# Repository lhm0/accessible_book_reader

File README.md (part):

# Accessible Book Reader

Software- und Hardware-Repository fuer den `Accessible Book Reader` (`ABR`).

## Lizenz

Der Accessible Book Reader ist ein Open-Source-/Open-Hardware-Projekt mit
starkem Copyleft. Wegen der unterschiedlichen Arten von Projektmaterial gilt
ein klar abgegrenztes Mehrfachlizenzmodell:

- eigener Software- und Firmwarecode: `GPL-3.0-or-later`
- eigene Elektronik-, Mechanik- und sonstige Hardwaredesigns:
  `CERN-OHL-S-2.0`
- Dokumentation und eindeutig eigene Medien: `CC-BY-SA-4.0`
- Fremdbibliotheken: unveraendert unter ihrer jeweiligen Originallizenz

Die mit Google Cloud Text-to-Speech erzeugten Systemansagen enthalten einen
eigenen [Herkunfts- und Nutzungshinweis](system_audio/messages/README.md).

Die GPL und CERN-OHL-S erlauben auch kommerzielle Nutzung, verlangen bei der
Weitergabe abgeleiteter Software beziehungsweise Hardware aber die jeweils
vorgesehene Bereitstellung des vollstaendigen Quellmaterials unter den
Copyleft-Bedingungen. Eine allgemeine Ausnahme fuer geschlossene kommerzielle
Weiterentwicklungen besteht nicht.

Die verbindliche Abgrenzung, Ausnahmen fuer Fremdcode und Hinweise zu nicht
mitlizenzierten Drittmaterialien stehen in [LICENSE.md](LICENSE.md); die
vollstaendigen Lizenztexte liegen unter [`LICENSES/`](LICENSES/). Hinweise zu
eingebundenem Fremdcode stehen in
[THIRD_PARTY_NOTICES.md](THIRD_PARTY_NOTICES.md). Fuer
Beitraege gelten [CONTRIBUTING.md](CONTRIBUTING.md) und die
[Contributor License Agreement](CLA.md). Die Contributor-Vereinbarung erhaelt
das Eigentum der Beitragenden, erlaubt dem Projektinhaber aber zusaetzlich eine
parallele kommerzielle Lizenzierung fuer spaetere Firmenkooperationen.
Firmenkooperationen, die von diesen oeffentlichen Lizenzen abweichen sollen,
erfordern einen separaten Entwicklungs- und Lizenzvertrag mit den jeweiligen
Rechteinhabern.

Es wurde keine Patent- oder Freedom-to-Operate-Recherche durchgefuehrt. Die
Lizenzen koennen nur Rechte einraeumen, ueber die der jeweilige Lizenzgeber
verfuegen darf; sie geben keine Zusicherung, dass Herstellung, Nutzung oder
Vertrieb keine Rechte Dritter beruehren. Der vollstaendige Hinweis und die
besondere Abgrenzung zwischen privatem Nachbau und kommerzieller Nutzung
stehen in [PATENT_NOTICE.md](PATENT_NOTICE.md).

Der Projektstand ist inzwischen ueber den reinen OCR-/TTS-Prototyp hinaus:

- realer Capture-Pfad mit `2` Pi-Kameras ist verifiziert
- `RapidOCR` laeuft stabil auf dem Pi
- `Google Cloud TTS` ist integriert
- Bedienpanel, NFC-Buchkontext, Seitenspeicherung und automatische
  Seitenausgabe sind implementiert
- E-Mail-Fernwartung fuer Datei-Download und kontrollierten Datei-Upload ist
  implementiert
- mehrere gespeicherte WLAN-Profile koennen automatisch ausgewaehlt oder
  gezielt umgeschaltet werden
- zentrale Buchsprachenprofile fuer Deutsch und U.S.-Englisch steuern
  Runtime-TTS, Kapitelansagen und die RapidOCR-Modellauswahl; Deutsch bleibt
  der kompatible Default
- neue NFC-Buecher speichern ihre Sprache dauerhaft in `book.json`; OCR,
  Ingest, Kapitel, Zusammenfassungen und TTS verhindern gemischte Buchdaten

Der aktuelle Entwicklungsschwerpunkt liegt jetzt auf:

- Stabilisierung und Feinschliff der neuen Abschnitts- und Summary-Ebene
- Langzeittest des integrierten PN5180-Zwei-Reader-Pfads mit
  `ISO14443A` und `ISO15693`

## Aktueller Produktpfad

Der derzeit bevorzugte reale Lauf auf dem Raspberry Pi 5 ist:

- Runtime: `hardware/control_panel_service.py`
- TTS fuer Seiten: `Google Cloud TTS`, Stimme aus dem aktiven Sprachprofil
- Systemhinweise: vorproduzierte WAV-Dateien aus dem Unterordner des aktiven
  Sprachprofils (`system_audio/messages/de/` oder `system_audio/messages/en/`)
- Buchidentifikation: `PN5180`-Gateway ueber UART
- Audiohardware: `MAX98357A` ueber I2S; ALSA-`default` muss systemweit per
  symbolischem Kartennamen auf diese Karte zeigen

Im Runtime-Pfad gilt aktuell:

- beim Start wird die PN5180-Abfrage sofort per `STATUS_START` angestossen
- die beiden Fotos werden aufgenommen, bevor das Ergebnis per `STATUS_FETCH`
  fuer Buchzuordnung und Orientierung abgeholt wird
- `ISO14443A` ist der fuehrende Buchschluessel; ein gleichzeitig gelesener
  `ISO15693`-Tag wird im Buchordner als alternative Zuordnung gespeichert
- Reader 2 kennzeichnet Orientierung 1: die beim Capture erzeugte
  Links-/Rechts-Zuordnung bleibt bestehen
- Reader 1 kennzeichnet Orientierung 2: `case/left.jpg` und
  `case/right.jpg` werden direkt nach `STATUS_FETCH` vertauscht
- danach wird `case/right.jpg` einmalig um `180` Grad gedreht; in der
  OCR-Vorverarbeitung erfolgt keine weitere feste Seitendrehung
- beide Seiten werden zuerst komplett aufgenommen
- danach wird links vor rechts verarbeitet
- Bildvorbereitung, OCR, `PageIngestor` und TTS starten zunaechst nur fuer die
  linke Seite
- waehrend die linke Seite bereits abgespielt wird, folgen Bildvorbereitung,
  OCR, `PageIngestor` und TTS fuer die rechte Seite

## Was Jetzt Implementiert Ist

### Laufende Geraetelogik

- langlebiger Frontpanel-Monitor
- `Start / Stop / NFC` fuer echten Lauf `capture -> Bildvorbereitung -> OCR -> page-ingest`
- Heartbeat-Signal waehrend der Wartezeit bis zur ersten Seitenaudio
- abbrechbare Seitenausgabe
- Lautstaerkeregelung ueber EC11-Flankeninterrupts mit threadsicherem
  Sollwert; wirkt blockweise auch waehrend `bing.wav` und Seitenaudio
- Buch-Loeschdialog ueber Dreifachtaste und `EC11`-Taster
- persistente, buchweise Nutzerstatistik fuer gescannte Seiten,
  Vorlesedauer und beide Zusammenfassungsfunktionen; taeglicher E-Mail-Report
  fuer den Zeitraum `04:00` bis `04:00`, auch an Tagen ohne Nutzung

### Buch- und Seitendaten

- Speicherung pro Buch unter `library/<TAG_ID>/`
- alternative ISO15693-Zuordnungen unter
  `library/<ISO14443A_TAG_ID>/iso15693_tag_ids.txt`
- `BookStore`
- `PageIngestor`
- `ChapterAssembler` fuer 10-20 Seiten lange Abschnitte mit Mid-Page-Grenzen
- `SummaryManager` fuer Abschnitts- und Gesamtzusammenfassungen ueber Gemini
- `PageRecord`-Ablage pro Seite
- `ChapterRecord`-Ablage pro Abschnitt
- `ScanRecord`-Ablage pro Doppelseite
- automatische Seitenausgabe auf Basis von `speak_text`

### Bereits sauber behandelte Textfaelle

- fehlende Seitenzahl auf nur einer Seite eines vollstaendigen Doppelseiten-
  Reports
- mehrere Kapitelmarker auf einer Seite
- reine Ueberschriftenseiten wie `INTERMEZZO`
- unvollstaendige Satzreste ueber Seiten hinweg
- Worttrennungen ueber Zeilen und ueber die linke/rechte Seitenkante
- gesperrt gesetzte Woerter wie `U E B E R S C H R I F T` werden fuer die
  Ausgabe ohne Buchstabenabstaende geschrieben
- kurze, vollstaendig grossgeschriebene Ueberschriften werden im
  `speak_text` lesbar geschrieben und als eigener Absatz markiert
- deutsche Vorlesetexte ersetzen `Dr.` durch `Doktor` und `Notre-Dame` durch
  `Notre Damm`; der originalgetreue `clean_text` bleibt unveraendert
  (bereits gespeicherte Seiten erhalten diese Ersetzungen erst bei erneutem
  Page-Ingest)
- kurze eingeklammerte OCR-Artefakte mit Ziffern werden nicht als Satzrest
  auf die Folgeseite uebernommen
- Kapitelansagen als Kardinalzahlen wie `Kapitel zwei`
- deutliche SSML-Pausen vor und nach Kapitelansagen

Wichtig zum aktuellen Satzrest-Verhalten:

- der Satzrest einer rechten Seite wird zusaetzlich unter
  `library/<TAG_ID>/state/pending_right_tail_fragment.json` gehalten
- fehlt bei einer frueh ingestierten linken Einzelseite die Seitenzahl, wird
  genau dieser Pending-Speicher fuer den Uebergang zur naechsten Seite genutzt

## Was Jetzt Neu Hinzugekommen Ist

- Abschnitte werden nach jedem Ingest aus vorhandenen `PageRecord`s gebildet
- Abschnittsenden liegen an der ersten erkannten Kapitelgrenze im Fenster
  `10..20` Seiten
- ohne Kapitelmarke endet ein Abschnitt am letzten vollstaendigen Absatz der
  `20.` Seite; die Folgegrenze wird persistent gespeichert
- abgeschlossene Abschnitte werden unter `library/<TAG_ID>/chapters/`
  gespeichert
- neue Abschnittszusammenfassungen werden direkt beim Erzeugen eines neuen
  Abschnitts ueber Gemini geschrieben
- `Kapitel-/Letzte-Seiten-Zusammenfassung` spricht die letzte
  Abschnittszusammenfassung, erzeugt oder aktualisiert sie bei Bedarf und
  signalisiert waehrenddessen per Intro plus `bing`-Heartbeat
- liegt nach dem letzten abgeschlossenen Abschnitt bereits weiterer Text vor,
  kombiniert dieselbe Taste dessen gespeicherte Zusammenfassung mit dem
  offenen Text zu einer temporaeren aktuellen Rueckschau; diese wird nur
  vorgelesen und nicht gespeichert
- vor dem ersten abgeschlossenen Abschnitt wird der vorhandene offene Text
  allein temporaer zusammengefasst
- `Buch-Zusammenfassung` erzeugt und spricht ein aktuelles
  "Was bisher geschah" in Kapitelreihenfolge, ebenfalls mit Intro plus
  `bing`-Heartbeat
- wenn noch keine Zusammenfassung vorliegt, spielt die Runtime
  `keine_zusammenfassung`

## Installation

Die README ist der Einstieg fuer eine Neuinstallation. Die ausfuehrliche,
hardwarebezogene Schritt-fuer-Schritt-Anleitung steht in
[docs/RASPBERRY_PI_SETUP.md](docs/RASPBERRY_PI_SETUP.md); der abschliessende
Funktionstest steht in
[docs/RASPBERRY_PI_SMOKETEST.md](docs/RASPBERRY_PI_SMOKETEST.md).

### 1. Raspberry Pi vorbereiten und Repository auschecken

Empfohlen ist Raspberry Pi OS Lite (64-bit). Nach dem ersten Boot und dem
Systemupdate werden die benoetigten Systempakete installiert:

```bash
sudo apt update
sudo apt full-upgrade -y
sudo apt install -y \
  git curl ca-certificates \
  build-essential pkg-config \
  python3 python3-venv python3-pip python3-dev \
  tesseract-ocr tesseract-ocr-deu \
  libgl1 libopenblas-dev \
  espeak-ng alsa-utils pulseaudio-utils \
  htop tmux

mkdir -p ~/src
git clone https://github.com/lhm0/accessible_book_reader.git ~/src/abr
cd ~/src/abr
```

Die Kameras, der Header-UART und der MAX98357A benoetigen zusaetzlich die in
[docs/RASPBERRY_PI_SETUP.md](docs/RASPBERRY_PI_SETUP.md) beschriebenen
Eintraege in `/boot/firmware/config.txt` sowie die dort dokumentierte
`/etc/asound.conf`. Die Repository-Datei `config.txt` ist eine Referenz fuer
die verifizierte Hardware, darf aber nicht ungeprueft eine vorhandene
Boot-Konfiguration ersetzen. Anschliessend neu starten und Kameras, UART und
Audio wie in der Setup-Anleitung pruefen.

Die Firmware und Verdrahtung des bevorzugten PN5180-Gateways sind unter
[hardware/pn5180_gateway/README.md](hardware/pn5180_gateway/README.md)
dokumentiert. Alternativ steht der PN532-Pfad unter
[hardware/pn532_gateway/README.md](hardware/pn532_gateway/README.md).

### 2. Python-Umgebung installieren

Empfohlen ist eine frische virtuelle Umgebung mit dem normalen `python3`,
nicht mit dem PlatformIO-Python und nicht aus einem anderen Rechner kopiert.

```bash
cd ~/src/abr
python3 -m venv .venv
source .venv/bin/activate
python -m pip install --upgrade pip
python -m pip install -e ".[ocr-rapidocr,dev,tts-google]"
```

Optional:

```bash
pip install ".[ocr-tesseract]"
pip install ".[ocr-paddle]"
```

### 3. Google Cloud fuer TTS und Zusammenfassungen einrichten

Der produktive Dienst benoetigt Application Default Credentials (`ADC`) eines
Google-Cloud-Projekts, in dem die verwendeten APIs und Abrechnung aktiviert
sind. Nach Installation des Google-Cloud-CLI fuer Raspberry Pi OS:

```bash
gcloud services enable \
  texttospeech.googleapis.com \
  aiplatform.googleapis.com \
  --project DEIN_PROJECT_ID
gcloud auth application-default login
gcloud auth application-default set-quota-project DEIN_PROJECT_ID
gcloud config set project DEIN_PROJECT_ID
```

Die Befehle legen die Anmeldedaten ausserhalb des Repositorys unter
`~/.config/gcloud/` ab. Keine Credential-Datei in das Projekt kopieren. Der
systemd-Installer setzt `HOME` auf das Home-Verzeichnis des installierenden
Benutzers, sodass der Dienst dieselben ADC-Daten findet. Alternativ kann ein
Service-Account ueber den von Google dokumentierten ADC-Mechanismus
bereitgestellt werden. Details und Testbefehle stehen in
[docs/RASPBERRY_PI_SETUP.md](docs/RASPBERRY_PI_SETUP.md).

### 4. Lokale Geraetekonfiguration und Dienste

Die Installer werden aus dem Repository mit `sudo` aufgerufen. Sie ermitteln
Benutzer, Home-Verzeichnis, Repository und `.venv` aus der aktuellen
Installation; ein bestimmter Benutzername oder absoluter Projektpfad ist
nicht erforderlich.

```bash
cd ~/src/abr
sudo deploy/install_language_switch.sh
sudo deploy/install_control_panel_service.sh
```

Damit wird `~/.config/abr/device.json` bei Bedarf mit Deutsch als Default
angelegt und der produktive Dienst installiert. Die Sprache kann danach mit
`sudo abr-language de` beziehungsweise `sudo abr-language en` gesetzt werden.
Details stehen in [docs/LANGUAGE_PROFILES.md](docs/LANGUAGE_PROFILES.md).

Weitere Funktionen sind optional:

```bash
# Gespeicherte NetworkManager-WLAN-Profile beim Boot vorbereiten
sudo deploy/install_wifi_autoconnect.sh

# Beim ersten Lauf mail.ini anlegen, dann ausfuellen und erneut aufrufen
sudo deploy/install_remote_mail.sh
sudo deploy/install_remote_mail.sh

# Erst nach eingerichteter mail.ini installieren
sudo deploy/install_usage_statistics.sh
```

WLAN-Zugangsdaten bleiben in NetworkManager; neue Profile werden mit den
Befehlen aus [docs/WIFI_PROFILES.md](docs/WIFI_PROFILES.md) interaktiv
angelegt. Die E-Mail-Konfiguration wird im folgenden Abschnitt sowie in
[docs/REMOTE_MAINTENANCE_EMAIL.md](docs/REMOTE_MAINTENANCE_EMAIL.md)
beschrieben.

### Lokale und generierte Konfigurationsdateien

| Pfad | Inhalt und Erzeugung | Im Repository? |
|---|---|---|
| `/boot/firmware/config.txt` | Kamera-, UART- und I2S-Konfiguration; manuell nach Pi-Setup-Anleitung | Nein |
| `/etc/asound.conf` | ALSA-Default fuer MAX98357A; manuell nach Pi-Setup-Anleitung | Nein |
| `~/.config/gcloud/` | Google ADC und Quota-Projekt; durch `gcloud` oder Service-Account | Nein |
| `~/.config/abr/device.json` | Buchsprache; durch `install_language_switch.sh` | Nein |
| `~/.config/abr/mail.ini` | Mailkonto und Empfaenger; neutrale Vorlage durch `install_remote_mail.sh` | Nein |
| NetworkManager-Profile | SSIDs und WLAN-Passwoerter; interaktiv mit `abr.wifi_profiles` | Nein |
| `/etc/systemd/system/abr-*.service` und `abr-*.timer` | Lokale Benutzer- und Projektpfade; durch die jeweiligen Dienst-Installer erzeugt | Nein |
| `calibration/out/cam0_planar.npz`, `cam1_planar.npz` | Mitgelieferte Referenzkalibrierung; fuer abweichende Kameramechanik neu erzeugen | Ja |

Es gibt keine erforderliche `.env`-Datei. API-Schluessel fuer optionale
experimentelle Backends werden nur ueber `OPENAI_API_KEY` beziehungsweise
`ELEVENLABS_API_KEY` aus der lokalen Prozessumgebung gelesen; der produktive
Google-Pfad verwendet ADC.

### 5. Installation pruefen

```bash
cd ~/src/abr
source .venv/bin/activate
python -m pytest -q
systemctl status abr-control-panel.service --no-pager -l
journalctl -u abr-control-panel.service -n 100 --no-pager
```

Danach den Hardware- und Runtime-Smoke-Test aus
[docs/RASPBERRY_PI_SMOKETEST.md](docs/RASPBERRY_PI_SMOKETEST.md)
durchfuehren.

### Lokale E-Mail-Konfiguration

Persoenliche Mailadressen, Benutzernamen und Passwoerter werden nicht im
Repository gespeichert. Der Mailbetrieb liest sie auf dem Raspberry Pi aus
`~/.config/abr/mail.ini`.

Eine Vorlage wird beim ersten Aufruf von
`sudo deploy/install_remote_mail.sh` mit Dateimodus `0600` angelegt. Danach
die lokale Datei bearbeiten:

```ini
[mail]
address = abr-device@example.com
recipient = owner@example.com
username = abr-device@example.com
password = PASSWORT_FUER_E_MAIL_PROGRAMME
smtp_host = smtp.example.com
smtp_port = 465
imap_host = imap.example.com
imap_port = 993
inbox = INBOX
```

`address` und `username` bezeichnen das Konto des Geraets. An `recipient`
gehen Fernwartungsdateien und Nutzungsberichte; nur exakt diese Adresse wird
zugleich als Absender fuer Upload-Mails akzeptiert. Die echten Werte bleiben
ausschliesslich in dieser lokalen, nicht versionierten Datei. Bei einer
bestehenden Installation ohne `recipient` wird aus Kompatibilitaetsgruenden
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
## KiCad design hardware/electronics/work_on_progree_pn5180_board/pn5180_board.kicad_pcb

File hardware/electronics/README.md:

# Electronics Uebersicht

Dieses Verzeichnis enthaelt die aktuellen KiCad-Hardwareprojekte des ABR-Aufbaus.

## Aktive Teilprojekte

- [abr_pi5_header](../../hardware/electronics/abr_pi5_header/abr_pi5_header.kicad_sch)
  - Hauptverdrahtung rund um den `Raspberry Pi 5`
  - Audio (`MAX98357A`), NFC-Anbindung, Bedien- und Lichtsignale

- [control_panel](../../hardware/electronics/control_panel/control_panel.kicad_sch)
  - separates Bedienpanel
  - `EC11` Drehencoder sowie Haupttaster wie `Button_Start`
  - eigene Produktionsdaten unter
    [production](../../hardware/electronics/control_panel/production)

- [LED_bar_long](../../hardware/electronics/LED_bar_long/LED_bar_long.kicad_sch)
  - aktuell gepflegte LED-Leiste fuer die Beleuchtung
  - Fertigungsdaten unter
    [production](../../hardware/electronics/LED_bar_long/production)

Aktueller Verdrahtungshinweis fuer den realen Scanneraufbau:

- die Beleuchtung wird jetzt getrennt links/rechts geschaltet
- `LED-left` haengt an einer MOSFET-Stufe auf `BCM12`
- `LED-right` haengt an einer MOSFET-Stufe auf `BCM13`

## Historischer Hinweis

Das fruehere Projekt `LED_bar_short` ist nicht mehr der aktive Pfad. Die aktuellen Arbeitsstaende liegen bei `LED_bar_long`, `control_panel` und `abr_pi5_header`.

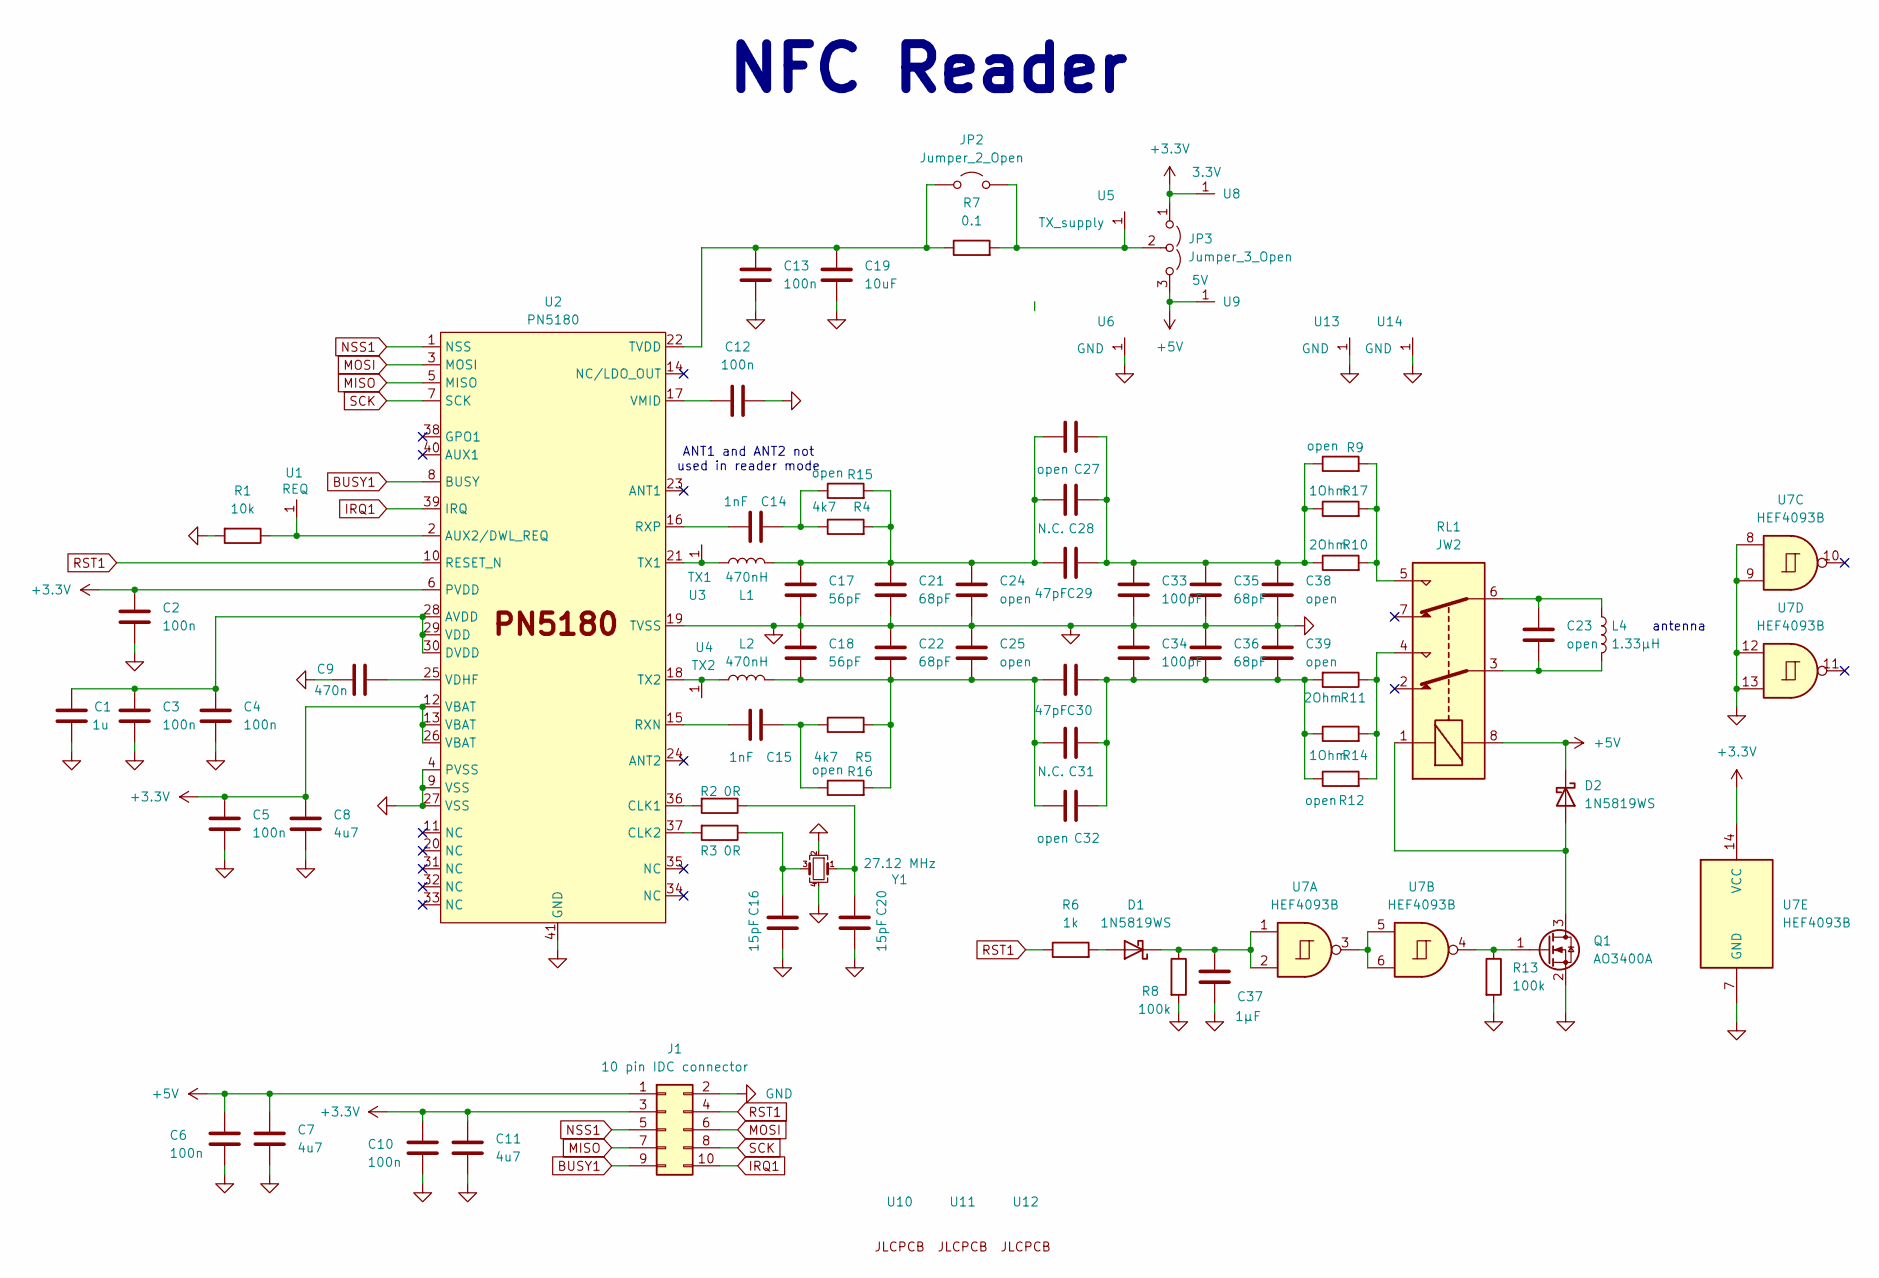
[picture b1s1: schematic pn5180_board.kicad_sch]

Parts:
C1: 1u; C_0603_1608Metric; LCSC C15849
C2, C3, C4, C5, C6, C10, C12, C13: 100n; C_0402_1005Metric; LCSC C1525
C7, C8, C11: 4u7; C_0603_1608Metric; LCSC C19666
C9: 470n; C_0603_1608Metric; LCSC C1623
C14, C15: 1nF; C_0402_1005Metric; LCSC C1523
C16, C20: 15pF; C_0402_1005Metric; LCSC C1548
C17, C18: 56pF; C_0603_1608Metric; LCSC C39148
C19: 10uF; C_0603_1608Metric; LCSC C96446
C21, C22, C35, C36: 68pF; C_0603_1608Metric; LCSC C28262
C23, C24, C25, C27, C32, C38, C39: open; C_aux
C28, C31: N.C.; C_0603_1608Metric
C29, C30: 47pF; C_0603_1608Metric; LCSC C1671
C33, C34: 100pF; C_0603_1608Metric; LCSC C14858
C37: 1µF; C_0603_1608Metric; LCSC C15849
D1, D2: 1N5819WS; D_SOD-323; LCSC C191023
J1: 10 pin IDC connector; IDC-Header_2x05_P2.54mm_Vertical_centered
JP2: Jumper_2_Open; SolderJumper-2_P1.3mm_Open_RoundedPad1.0x1.5mm
JP3: Jumper_3_Open; SolderJumper-3_P1.3mm_Open_RoundedPad1.0x1.5mm
L1, L2: 470nH; L_0603_1608Metric; LCSC C341701
L4: 1.33µH; NFC_antenna
Q1: AO3400A; SOT-23; LCSC C20917
R1: 10k; R_0402_1005Metric; LCSC C25744
R2, R3: 0R; R_0402_1005Metric; LCSC C17168
R4, R5: 4k7; R_0402_1005Metric; LCSC C25900
R6: 1k; R_0402_1005Metric; LCSC C11702
R7: 0.1; R_1206_3216Metric; LCSC C25334
R8, R13: 100k; R_0402_1005Metric; LCSC C25741
R9, R12, R15, R16: open; R_Axial_DIN0207_L6.3mm_D2.5mm_P10.16mm_Horizontal
R10, R11: 2Ohm; R_0603_1608Metric; LCSC C22977
R14, R17: 1Ohm; R_0603_1608Metric; LCSC C22936
RL1: JW2; Relay
U1: REQ; 1pin
U2: PN5180; HVQFN-40-1EP_6x6mm_P0.5mm_EP4.1x4.1mm_ThermalVias; LCSC C1526287
U3: TX1; 1pin
U4: TX2; 1pin
U5: TX_supply; 1pin
U6, U13, U14: GND; 1pin
U7: HEF4093B; SOIC-14_3.9x8.7mm_P1.27mm; LCSC C5456626
U8: 3.3V; 1pin
U9: 5V; 1pin
U10, U11, U12: JLC_tooling_hole
Y1: 27.12 MHz; Crystal_SMD_4Pin_A_3.2x2.5mm; LCSC C29975

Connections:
+3.3V: C2.1, C5.1, C8.1, C10.1, C11.1, J1.3, JP3.1 (A), U2.6 (PVDD), U2.12 (VBAT), U2.13 (VBAT), U2.26 (VBAT), U7.14 (VCC), U8.1 (pin)
+5V: C6.1, C7.1, D2.1 (K), J1.1, JP3.3 (B), RL1.8, U9.1 (pin)
BUSY1: J1.9, U2.8 (BUSY)
GND: C1.2, C2.2, C3.2, C4.2, C5.2, C6.2, C7.2, C8.2, C9.1, C10.2, C11.2, C12.2, C13.2, C16.2, C17.2, C18.1, C19.2, C20.2, C21.2, C22.1, C24.1, C25.2, C33.1, C34.2, C35.1, C36.2, C37.2, C38.1, C39.2, J1.2, Q1.2 (S), R1.2, R8.2, R13.2, U2.4 (PVSS), U2.9 (VSS), U2.19 (TVSS), U2.27 (VSS), U2.41 (GND), U6.1 (pin), U7.7 (GND), U7.8, U7.9, U7.12, U7.13, U13.1 (pin), U14.1 (pin), Y1.2, Y1.4
IRQ1: J1.10, U2.39 (IRQ)
MISO: J1.7, U2.5 (MISO)
MOSI: J1.6, U2.3 (MOSI)
NSS1: J1.5, U2.1 (NSS)
unnamed: C14.2, R4.1, R15.1
unnamed: C15.2, R5.1, R16.1
unnamed: C16.1, R3.1, Y1.3
unnamed: C17.1, C21.1, C24.2, C27.1, C28.1, C29.1, L1.2, R4.2, R15.2
unnamed: C18.2, C22.2, C25.1, C30.1, C31.1, C32.1, L2.2, R5.2, R16.2
unnamed: C20.1, R2.1, Y1.1
unnamed: C23.1, L4.2, RL1.3
unnamed: C23.2, L4.1, RL1.6
unnamed: C27.2, C28.2, C29.2, C33.2, C35.2, C38.2, R9.1, R10.1, R17.1
unnamed: C30.2, C31.2, C32.2, C34.1, C36.1, C39.1, R11.2, R12.1, R14.1
unnamed: D1.2 (A), R6.2
unnamed: C37.1, D1.1 (K), R8.1, U7.1, U7.2
unnamed: D2.2 (A), Q1.3 (D), RL1.1
unnamed: C13.1, C19.1, JP2.1 (A), R7.1, U2.22 (TVDD)
unnamed: JP2.2 (B), JP3.2 (C), R7.2, U5.1 (pin)
unnamed: Q1.1 (G), R13.1, U7.4
unnamed: R9.2, R10.2, R17.2, RL1.5
unnamed: R11.1, R12.2, R14.2, RL1.4
unnamed: R1.1, U1.1 (pin), U2.2 (AUX2/DWL_REQ)
unnamed: C1.1, C3.1, C4.1, U2.28 (AVDD), U2.29 (VDD), U2.30 (DVDD)
unnamed: R2.2, U2.36 (CLK1)
unnamed: R3.2, U2.37 (CLK2)
unnamed: C15.1, U2.15 (RXN)
unnamed: C14.1, U2.16 (RXP)
unnamed: L1.1, U2.21 (TX1), U3.1 (pin)
unnamed: L2.1, U2.18 (TX2), U4.1 (pin)
unnamed: C9.2, U2.25 (VDHF)
unnamed: C12.1, U2.17 (VMID)
unnamed: U7.3, U7.5, U7.6
RST1: J1.4, R6.1, U2.10 (RESET_N)
SCK: J1.8, U2.7 (SCK)

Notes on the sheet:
antenna
ANT1 and ANT2 not used in reader mode
NFC Reader

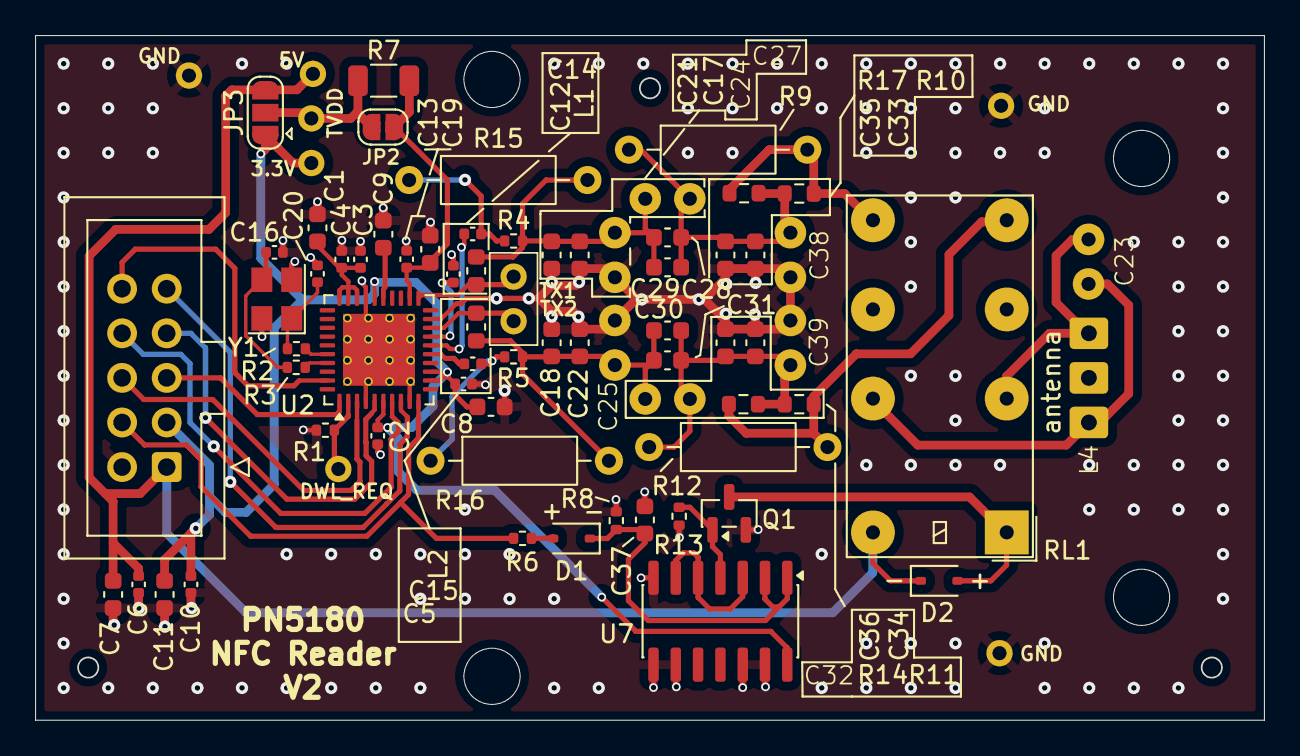
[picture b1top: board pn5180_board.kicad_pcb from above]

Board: 2 copper layers, 70.0 x 39.0 mm, 80 parts (0 on the bottom side), 39 nets.

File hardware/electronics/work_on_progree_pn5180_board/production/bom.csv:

Designator,Footprint,Quantity,Value,LCSC Part #
C1,0603,1,1u,C15849
"C10, C12, C13, C2, C3, C4, C5, C6",0402,8,100n,C1525
"C11, C7, C8",0603,3,4u7,C19666
"C14, C15",0402,2,1nF,C1523
"C16, C20",0402,2,15pF,C1548
"C17, C18",0603,2,56pF,C39148
C19,0603,1,10uF,C96446
"C21, C22, C35, C36",0603,4,68pF,C28262
"C23, C38, C39",C_aux,3,open,
"C24, C25, C27, C32",C_aux,4,open,
"C28, C31",0603,2,N.C.,
"C29, C30",0603,2,47pF,C1671
"C33, C34",0603,2,100pF,C14858
C37,0603,1,1µF,C15849
C9,0603,1,470n,C1623
"D1, D2",D_SOD-323,2,1N5819WS,C191023
J1,IDC-Header_2x05_P2.54mm_Vertical_centered,1,10 pin IDC connector,
JP2,SolderJumper-2_P1.3mm_Open_RoundedPad1.0x1.5mm,1,Jumper_2_Open,
"L1, L2",0603,2,470nH,C341701 
L4,NFC_antenna,1,1.33µH,
Q1,SOT-23,1,AO3400A,C20917
R1,0402,1,10k,C25744
"R10, R11",0603,2,2Ohm,C22977
"R12, R15, R16, R9",R_Axial_DIN0207_L6.3mm_D2.5mm_P10.16mm_Horizontal,4,open,
"R13, R8",0402,2,100k,C25741
"R14, R17",0603,2,1Ohm,C22936
"R2, R3",0402,2,0R,C17168
"R4, R5",0402,2,4k7,C25900
R6,0402,1,1k,C11702
R7,1206,1,0.1,C25334
RL1,Relay,1,JW2,
U1,1pin,1,REQ,
"U10, U11, U12",JLC_tooling_hole,3,~,
"U13, U14, U6",1pin,3,GND,
U2,HVQFN-40-1EP_6x6mm_P0.5mm_EP4.1x4.1mm_ThermalVias,1,PN5180,C1526287
U3,1pin,1,TX1,
U4,1pin,1,TX2,
U5,1pin,1,TX_supply,
U7,SOIC-14_3.9x8.7mm_P1.27mm,1,HEF4093B,C5456626
U8,1pin,1,3.3V,
U9,1pin,1,5V,
Y1,Crystal_SMD_4Pin_A_3.2x2.5mm,1,27.12 MHz,C29975

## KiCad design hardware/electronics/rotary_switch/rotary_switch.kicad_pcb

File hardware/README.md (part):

# Hardware Uebersicht

Dieses Verzeichnis enthaelt die hardwarebezogenen Teilprojekte fuer den
aktuellen ABR-Scannerstand.

## Struktur

- [pn532_gateway](../hardware/pn532_gateway/README.md)
  - RP2040-/Pico-Gateway fuer `2 x PN532`
  - UART-Protokoll zum `Raspberry Pi 5`
  - weiterhin als alternativer NFC-Pfad im Repo

- [pn5180_gateway](../hardware/pn5180_gateway/README.md)
  - RP2040-/Pico-Gateway fuer bis zu `2 x PN5180`
  - aktueller produktiver Buchkennungs-Pfad
  - aktueller technischer Arbeitsstand: `2 x PN5180`, sequentielle
    Reader-Freigabe ueber `RESET`, on-demand statt Polling

- [electronics](../hardware/electronics/README.md)
  - KiCad-Projekte fuer Pi-Header, Bedienpanel und LED-Bar

- [mechanics](../hardware/mechanics/README.md)
  - Fusion- und Exportdateien fuer den Scanneraufbau

## Wichtige Pi-Skripte

- [capture_double_page.py](../hardware/capture_double_page.py)
  - produktionsnaher Zwei-Kamera-Capture
  - schaltet `LED-left` und `LED-right` passend zur Aufnahme
  - erzeugt `raw`, `rectified`, `case`, `ocr` und `debug/page_1..2`
  - `--no-denoise` ist aktuell der bevorzugte schnelle Pfad

- [run_rapidocr.py](../hardware/run_rapidocr.py)
  - schlanker RapidOCR-Wrapper fuer vorbereitete `ocr/left.png` und
    `ocr/right.png`
  - schreibt `left.txt`, `right.txt` und `report.json`
  - bevorzugter Standard: `--orientation-mode off`

- [camera_test_server.py](../hardware/camera_test_server.py)
  - Browser-Livebildtest fuer die Pi-Kameras
  - optionales Fadenkreuz
  - Review-Modus fuer `raw`, `rectified`, `enhanced` und `ocr-overlay`

- [led_light_test.py](../hardware/led_light_test.py)
  - einfacher Test fuer `LED-left` auf `BCM12` und `LED-right` auf `BCM13`

- [control_panel_test.py](../hardware/control_panel_test.py)
  - einfacher GPIO-Test fuer Taster und `EC11`

- [control_panel_service.py](../hardware/control_panel_service.py)
  - aktueller produktionsnaher Runtime-Dienst
  - startet den echten Lauf `capture -> Bildvorbereitung -> OCR -> page-ingest`
  - liest Buch-Tags ueber NFC-Gateway
  - startet die PN5180-Abfrage beim Tastendruck mit `STATUS_START` und holt
    sie nach beiden Aufnahmen mit `STATUS_FETCH` ab
  - verwendet ISO14443A als fuehrende Buch-ID und ISO15693 als gespeicherte
    alternative Zuordnung
  - ordnet die Kamerabilder anhand des ISO14443A-Readers zu:
    Orientierung 1 behaelt links/rechts, Orientierung 2 vertauscht beide
  - dreht danach `case/right.jpg` einmalig um 180 Grad
  - speichert Ergebnisse unter `library/<tag_id>/`
  - nimmt beide Seiten zuerst komplett auf
  - verarbeitet danach links vor rechts
  - startet die Seitenausgabe, sobald die linke Seite als Audio vorliegt
  - zieht die rechte Seite waehrend der linken Wiedergabe nach
  - spielt nach vollstaendig beendeter rechter Seitenausgabe `tatata.wav` als
    Umblättersignal; Stop, TTS-Fehler und Wiedergabefehler unterdruecken es
  - spielt vor dem Start `bing`
  - spielt waehrend des Wartens einen Heartbeat mit erneutem `bing`
  - beendet den Heartbeat sauber bei Erfolg, Stop oder Fehler
  - spielt bei nicht vorlesbarem Ingest-Ergebnis `fehler`
  - stoppt eine laufende Seitenausgabe per `Start / Stop`
  - unterstuetzt den Buch-Loeschdialog per Dreifachtaste
  - erzeugt neue Abschnittszusammenfassungen direkt nach neuer
    Abschnittsbildung
  - spielt bei den beiden Summary-Tasten zuerst
    `kapitel_zusammenfassen` bzw. `buch_zusammenfassen`
  - startet danach einen `bing`-Heartbeat bis die Summary-Audio bereit ist
  - spielt `keine_zusammenfassung`, wenn noch kein passender Summary-Text
    verfuegbar ist
  - unterstuetzt konfigurierbares Artefakt-Cleanup

- [page_ingest_debug.py](../hardware/page_ingest_debug.py)
  - Offline-Debugpfad fuer `report.json -> PageRecord -> BookStore`

- [generate_audio_message.py](../hardware/generate_audio_message.py)
  - erzeugt vorproduzierte Audio-Botschaften fuer Systemhinweise
  - Standardstimme: `Google Cloud TTS`, `de-DE-Standard-A`
  - Standardpfad: `system_audio/messages`
  - `--ssml` erlaubt `<break .../>`
  - fuer Raspi-only-Erzeugung ohne Git-Konflikte sollte `--output-root`
    ausserhalb des Repo-Pfads verwendet werden

## Aktueller Runtime-Pfad

Die aktuelle Pi-Laufzeit besteht aus:

1. GPIO-Flankeninterrupts fuer EC11 A/B und Taster-Polling ueber
   `FrontPanelMonitor`; `pinctrl` bleibt Encoder-Polling-Fallback
2. Action-Routing zu fachlichen Aktionen
3. `RuntimeController`
4. `ForegroundJobManager` fuer `capture -> Bildvorbereitung -> OCR -> page-ingest`
5. `PageIngestService`
6. `PageAudioPlayer`
7. `SystemAudio` fuer Warnhinweise

Die EC11-Interruptbehandlung aktualisiert nur einen threadsicheren
Lautstaerke-Sollwert. Seiten- und Systemaudio fragen ihn waehrend der
Wiedergabe blockweise ab. Der dynamische `aplay`-Pfad arbeitet mit `250ms`
PCM-Vorlauf, `300ms` ALSA-Puffer und `50ms` Perioden; jeder PCM-Block wird
sofort geflusht. Damit bleibt insbesondere `bing.wav` trotz laufender
Lautstaerkeregelung zusammenhaengend.

Produktiv verdrahtet sind jetzt zusaetzlich:

- `Buch-Zusammenfassung`
- `Kapitel-/Letzte-Seiten-Zusammenfassung`
- `ChapterAssembler`
- `SummaryManager`

Pi-Audio-Voraussetzung:

- `/etc/asound.conf` definiert das globale ALSA-`default` als `plug`-PCM fuer
  `hw:CARD=MAX98357A,DEV=0`
- der symbolische Kartenname ist verbindlich; numerische Kartenindizes koennen
  durch die beiden HDMI-Karten wechseln
- Setup, Referenztests und Fehlerbild `Unknown error 524` stehen in
  [docs/RASPBERRY_PI_SETUP.md](../docs/RASPBERRY_PI_SETUP.md)

Wichtig:

- `SummaryService` existiert weiterhin als allgemeine asynchrone
  Hilfskomponente im Repo
- der produktive `control_panel_service` verwendet aktuell aber direkt den
  `SummaryManager`

## Pi-Referenzkommando

Dieses Kommando dient dem manuellen Test. Fuer den Dauerbetrieb wird
`abr-control-panel.service` verwendet. Die vollstaendige Einrichtung und
Diagnose steht in
[docs/SYSTEMD_CONTROL_PANEL_SERVICE.md](../docs/SYSTEMD_CONTROL_PANEL_SERVICE.md).

```bash
cd ~/src/abr
source .venv/bin/activate
python hardware/control_panel_service.py \
  --gpio-backend auto \
  --job-mode capture-ocr \
  --library-root library \
  --nfc-mode gateway \
  --page-tts-speed 0.85 \
  --chapter-summary-target-pages 1.5 \
  --book-summary-target-pages 1.5
```

Nuetzliche Optionen:

- `--artifact-mode debug|production`
- `--cleanup-stage after-ocr|after-ingest`
- `--page-tts-backend google|google-standard-enhanced|google-neural2|google-gemini-flash`
- `--page-tts-speed 0.9`
- `--volume-mixer-control auto`
- `--summary-gemini-model gemini-3.5-flash`
- `--summary-gcp-project <PROJECT_ID>`
- `--summary-gcp-location global`
- `--chapter-summary-target-pages 1.5`
- `--book-summary-target-pages 1.5`

Bei beiden Summary-Parametern entspricht eine Zielseite `250` Woertern.
Beispielsweise erzeugt `0.5` eine Zielgrenze von `125` Woertern. Wird diese
Grenze um mehr als zehn Prozent ueberschritten, kuerzt Gemini das Ergebnis in
einem zweiten Durchlauf.

Die Taste `Kapitel-/Letzte-Seiten-Zusammenfassung` beruecksichtigt auch Text,
der nach dem letzten abgeschlossenen Abschnitt aufgenommen wurde. Der
`ChapterAssembler` liest ihn ab seiner persistenten offenen Abschnittsgrenze.
Gemini verbindet ihn mit der gespeicherten Zusammenfassung des letzten
Abschnitts. Diese aktuelle Zwischenzusammenfassung wird nur vorgelesen und
nicht unter `summaries/` gespeichert. Existiert noch kein fertiger Abschnitt,
wird der bisherige offene Text allein temporaer zusammengefasst.

Zur Seitensprache:

- `google` bleibt der unveraenderte Default mit `de-DE-Standard-H`
- `google-standard-enhanced` verwendet dieselbe Standard-H-Stimme und
  dasselbe Backend, strukturiert den Text aber mit SSML fuer Saetze,
  Absaetze und Ueberschriften; bei Fragen wird das vollstaendige letzte Wort
  um drei Halbtoene angehoben; nach Saetzen innerhalb eines Absatzes liegen
  `900ms`, nach dem letzten Satz eines Absatzes stattdessen `2000ms` Pause.
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
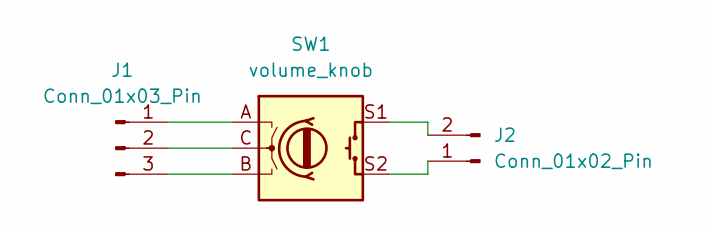
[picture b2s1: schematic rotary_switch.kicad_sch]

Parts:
J1: Conn_01x03_Pin; 3_pin
J2: Conn_01x02_Pin; 2_pin
SW1: volume_knob; RotaryEncoder_Alps_EC11E-Switch_Vertical_H20mm

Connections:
unnamed: J1.1, SW1.A
unnamed: J1.2, SW1.C
unnamed: J1.3, SW1.B
unnamed: J2.1, SW1.S2
unnamed: J2.2, SW1.S1

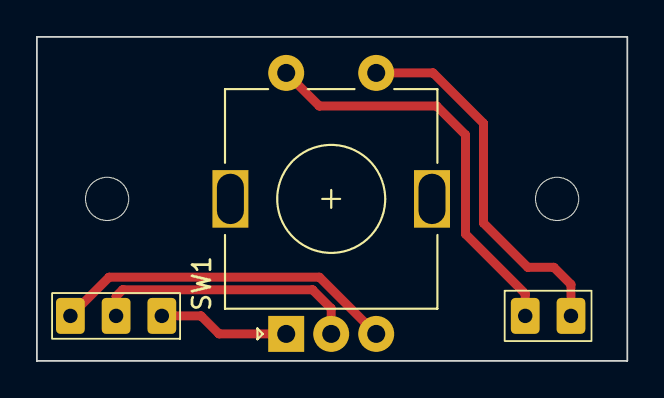
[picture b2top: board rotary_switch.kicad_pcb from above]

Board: 2 copper layers, 32.8 x 18.0 mm, 3 parts (0 on the bottom side), 5 nets.

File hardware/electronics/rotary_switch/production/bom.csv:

Designator,Footprint,Quantity,Value,LCSC Part #
J1,3_pin,1,Conn_01x03_Pin,
J2,2_pin,1,Conn_01x02_Pin,
SW1,RotaryEncoder_Alps_EC11E-Switch_Vertical_H20mm,1,volume_knob,

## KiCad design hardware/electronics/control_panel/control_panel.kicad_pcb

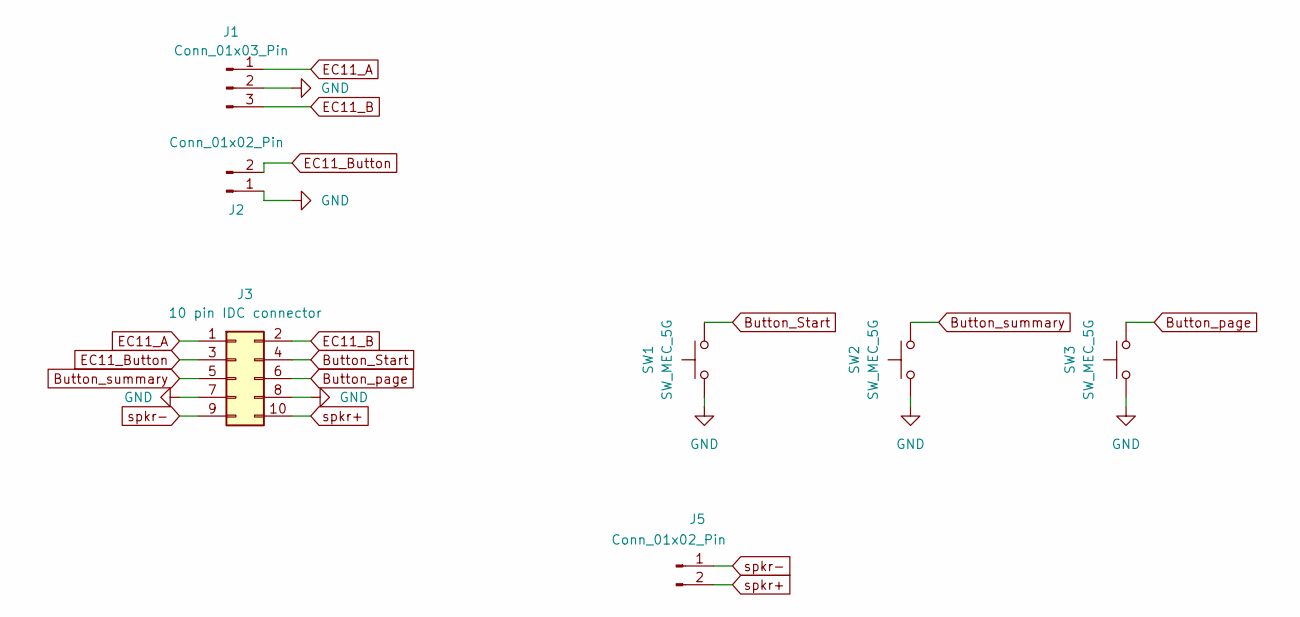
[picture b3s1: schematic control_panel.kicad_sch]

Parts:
J1: Conn_01x03_Pin; 3_pin
J2, J5: Conn_01x02_Pin; 2_pin
J3: 10 pin IDC connector; IDC-Header_2x05_P2.54mm_Vertical_centered
SW1, SW2, SW3: SW_MEC_5G; OmronTaster

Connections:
Button_Start: J3.4, SW1.2 (B)
Button_page: J3.6, SW3.2 (B)
Button_summary: J3.5, SW2.2 (B)
EC11_A: J1.1, J3.1
EC11_B: J1.3, J3.2
EC11_Button: J2.2, J3.3
GND: J1.2, J2.1, J3.7, J3.8, SW1.1 (A), SW2.1 (A), SW3.1 (A)
spkr+: J3.10, J5.2
spkr-: J3.9, J5.1

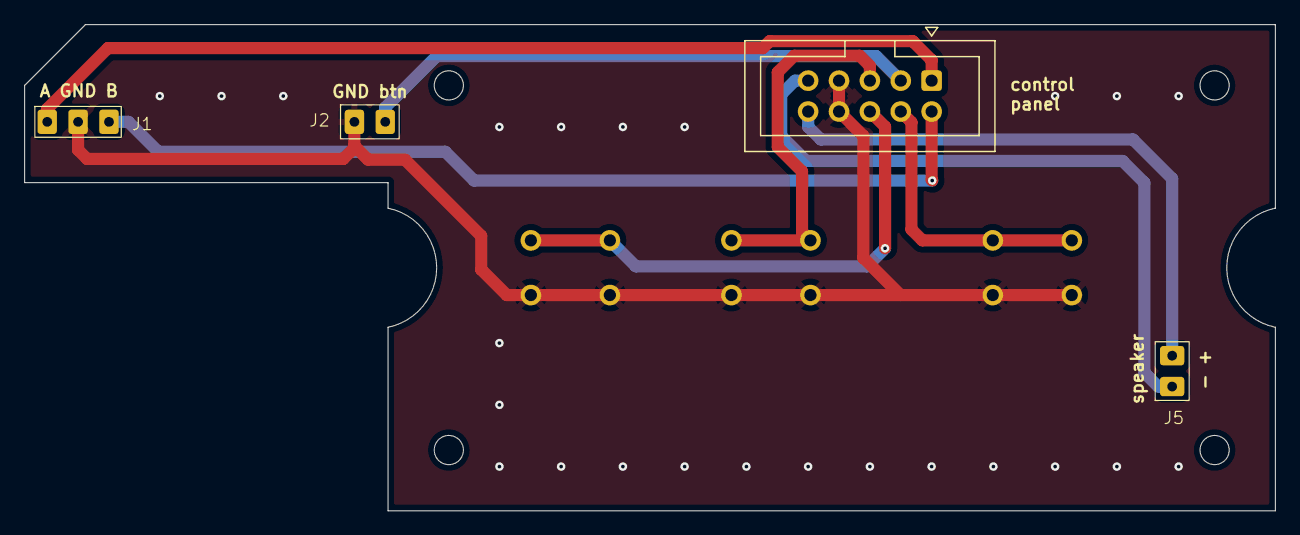
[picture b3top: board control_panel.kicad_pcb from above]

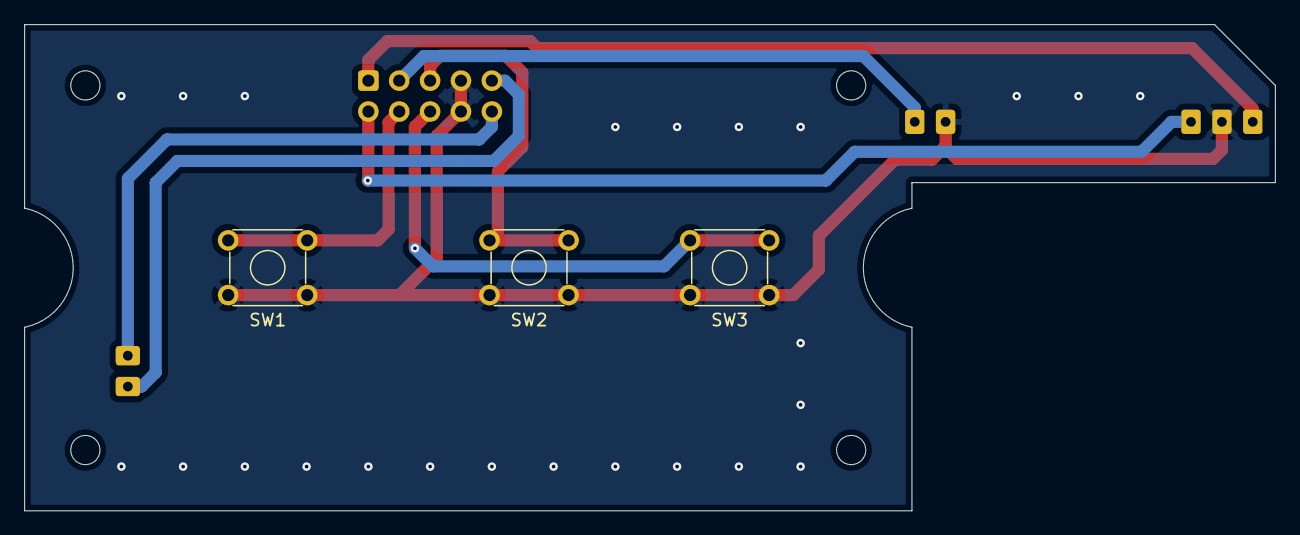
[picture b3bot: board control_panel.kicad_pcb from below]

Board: 2 copper layers, 102.9 x 40.0 mm, 7 parts (3 on the bottom side), 9 nets.

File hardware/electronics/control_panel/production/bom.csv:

Designator,Footprint,Quantity,Value,LCSC Part #
J1,3_pin,1,Conn_01x03_Pin,
"J2, J5",2_pin,2,Conn_01x02_Pin,
J3,IDC-Header_2x05_P2.54mm_Vertical_centered,1,10 pin IDC connector,
"SW1, SW2, SW3",OmronTaster,3,SW_MEC_5G,

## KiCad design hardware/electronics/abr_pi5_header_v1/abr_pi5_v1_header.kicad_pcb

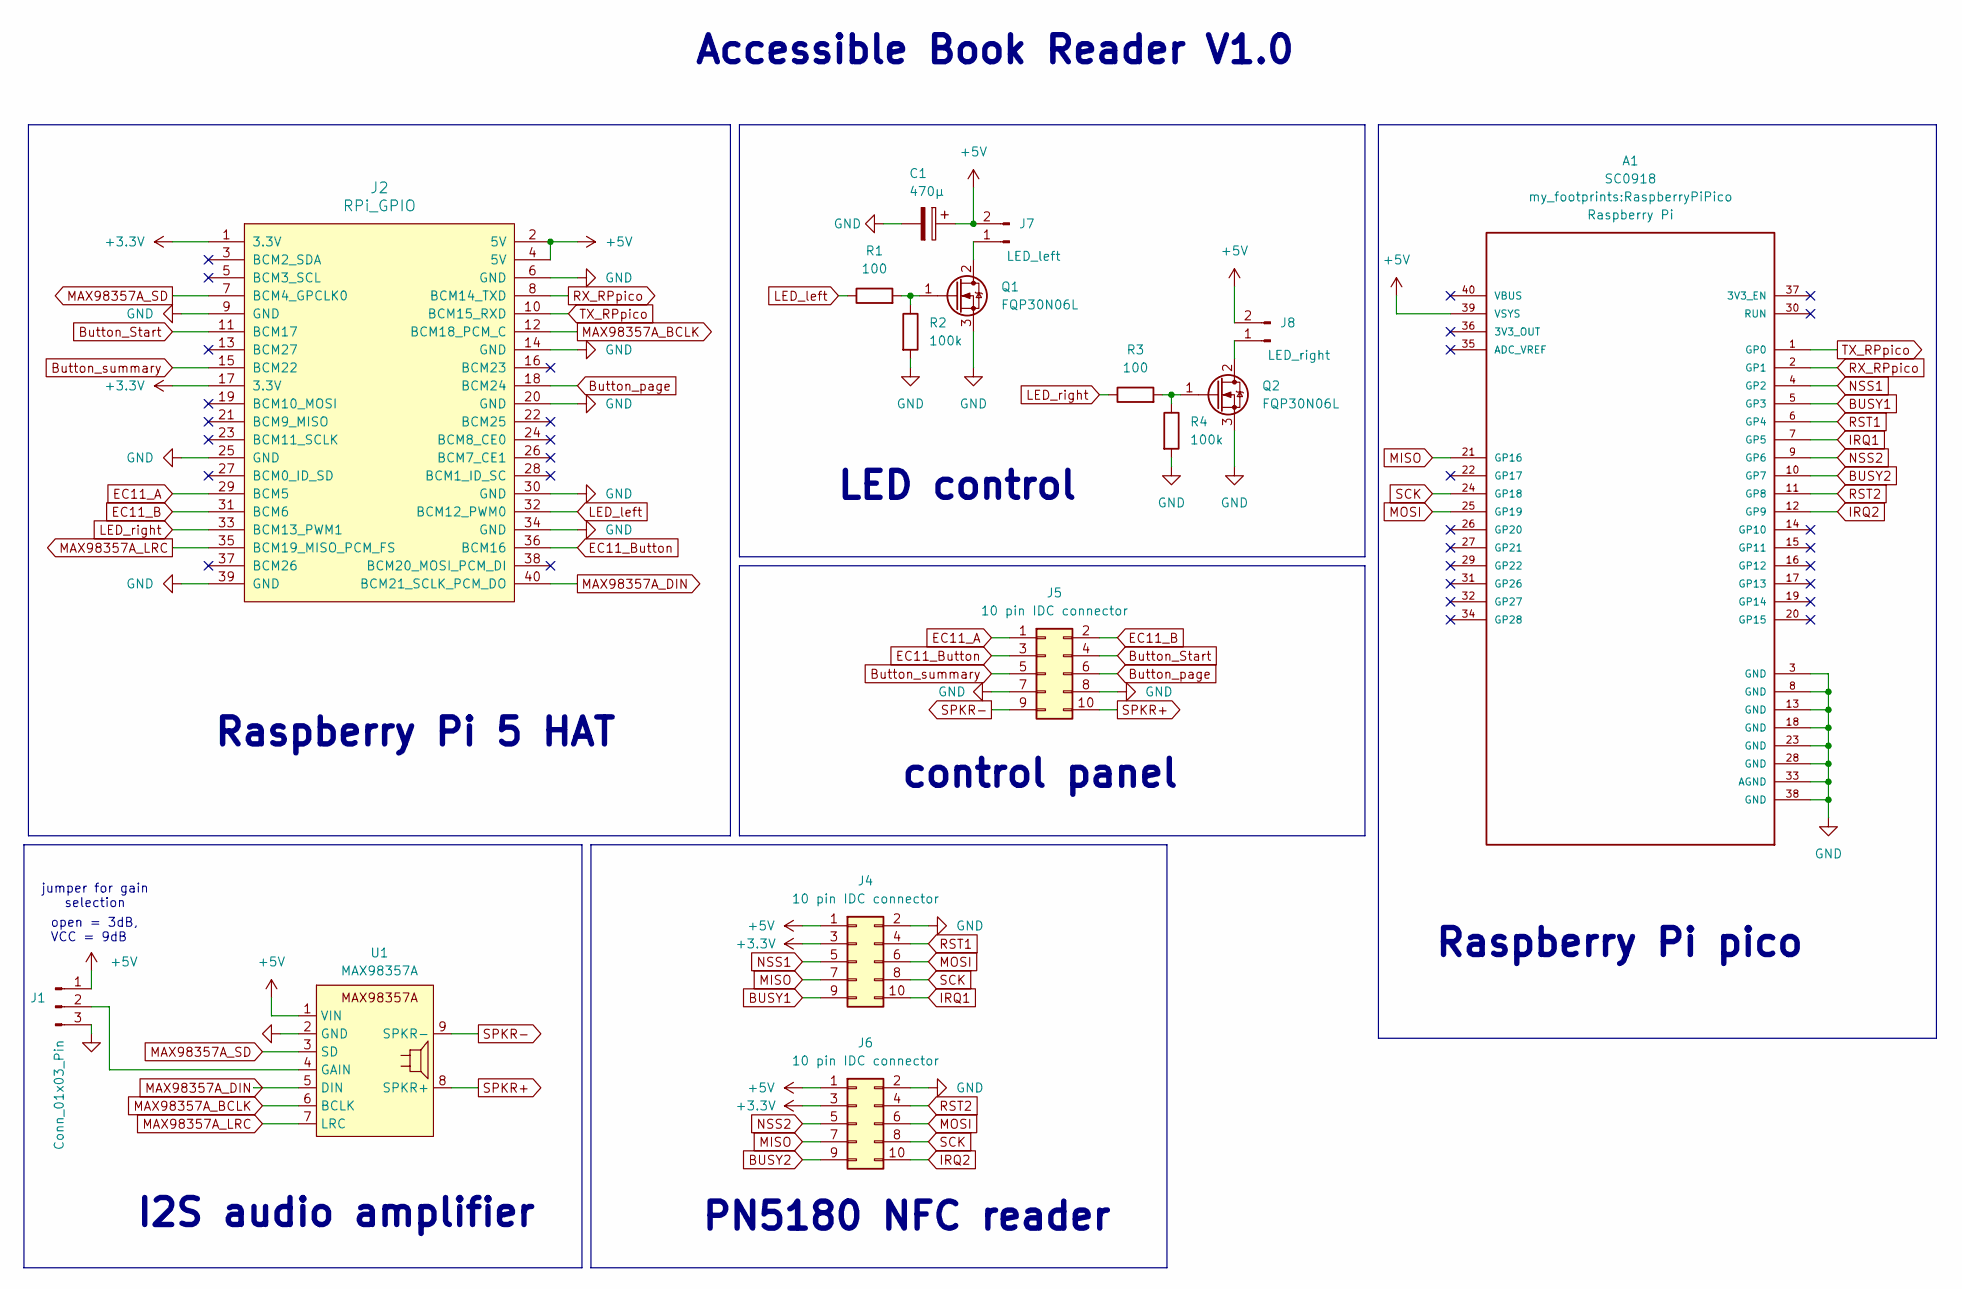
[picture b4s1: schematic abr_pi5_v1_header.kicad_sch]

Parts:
A1: SC0918; RaspberryPiPico; PARTREV 1.6
C1: 470µ; CP_Radial_D10.0mm_P5.00mm_slim_silkscreen
J1: Conn_01x03_Pin; 3_pin_jumper
J2: RPi_GPIO; RPI_HAT_back
J4, J5, J6: 10 pin IDC connector; IDC-Header_2x05_P2.54mm_Vertical_centered
J7: LED_left; JST_XH_B2B-XH-A_1x02_P2.50mm_Vertical
J8: LED_right; JST_XH_B2B-XH-A_1x02_P2.50mm_Vertical
Q1, Q2: FQP30N06L; TO220_vertikal
R1, R3: 100; R_Axial_DIN0207_L6.3mm_D2.5mm_P10.16mm_Horizontal
R2, R4: 100k; R_Axial_DIN0207_L6.3mm_D2.5mm_P10.16mm_Horizontal
U1: MAX98357A; MAX98357A_breakout

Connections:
+3.3V: J2.1 (3.3V), J2.17 (3.3V), J4.3, J6.3
+5V: A1.39 (VSYS), C1.1, J1.1, J2.2 (5V), J2.4 (5V), J4.1, J6.1, J7.2, J8.2, U1.1 (VIN)
BUSY1: A1.5 (GP3), J4.9
BUSY2: A1.10 (GP7), J6.9
Button_Start: J2.11 (BCM17), J5.4
Button_page: J2.18 (BCM24), J5.6
Button_summary: J2.15 (BCM22), J5.5
EC11_A: J2.29 (BCM5), J5.1
EC11_B: J2.31 (BCM6), J5.2
EC11_Button: J2.36 (BCM16), J5.3
GND: A1.3 (GND), A1.8 (GND), A1.13 (GND), A1.18 (GND), A1.23 (GND), A1.28 (GND), A1.33 (AGND), A1.38 (GND), C1.2, J1.3, J2.6 (GND), J2.9 (GND), J2.14 (GND), J2.20 (GND), J2.25 (GND), J2.30 (GND), J2.34 (GND), J2.39 (GND), J4.2, J5.7, J5.8, J6.2, Q1.3 (S), Q2.3 (S), R2.2, R4.2, U1.2 (GND)
IRQ1: A1.7 (GP5), J4.10
IRQ2: A1.12 (GP9), J6.10
LED_left: J2.32 (BCM12_PWM0), R1.1
LED_right: J2.33 (BCM13_PWM1), R3.1
MAX98357A_BCLK: J2.12 (BCM18_PCM_C), U1.6 (BCLK)
MAX98357A_DIN: J2.40 (BCM21_SCLK_PCM_DO), U1.5 (DIN)
MAX98357A_LRC: J2.35 (BCM19_MISO_PCM_FS), U1.7 (LRC)
MAX98357A_SD: J2.7 (BCM4_GPCLK0), U1.3 (SD)
MISO: A1.21 (GP16), J4.7, J6.7
MOSI: A1.25 (GP19), J4.6, J6.6
NSS1: A1.4 (GP2), J4.5
NSS2: A1.9 (GP6), J6.5
unnamed: J1.2, U1.4 (GAIN)
unnamed: J7.1, Q1.2 (D)
unnamed: J8.1, Q2.2 (D)
unnamed: Q1.1 (G), R1.2, R2.1
unnamed: Q2.1 (G), R3.2, R4.1
RST1: A1.6 (GP4), J4.4
RST2: A1.11 (GP8), J6.4
RX_RPpico: A1.2 (GP1), J2.8 (BCM14_TXD)
SCK: A1.24 (GP18), J4.8, J6.8
SPKR+: J5.10, U1.8 (SPKR+)
SPKR-: J5.9, U1.9 (SPKR-)
TX_RPpico: A1.1 (GP0), J2.10 (BCM15_RXD)

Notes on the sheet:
control panel
LED control
Accessible Book Reader V1.0
PN5180 NFC reader
jumper for gain selection
open = 3dB, VCC = 9dB
I2S audio amplifier
Raspberry Pi 5 HAT
Raspberry Pi pico
